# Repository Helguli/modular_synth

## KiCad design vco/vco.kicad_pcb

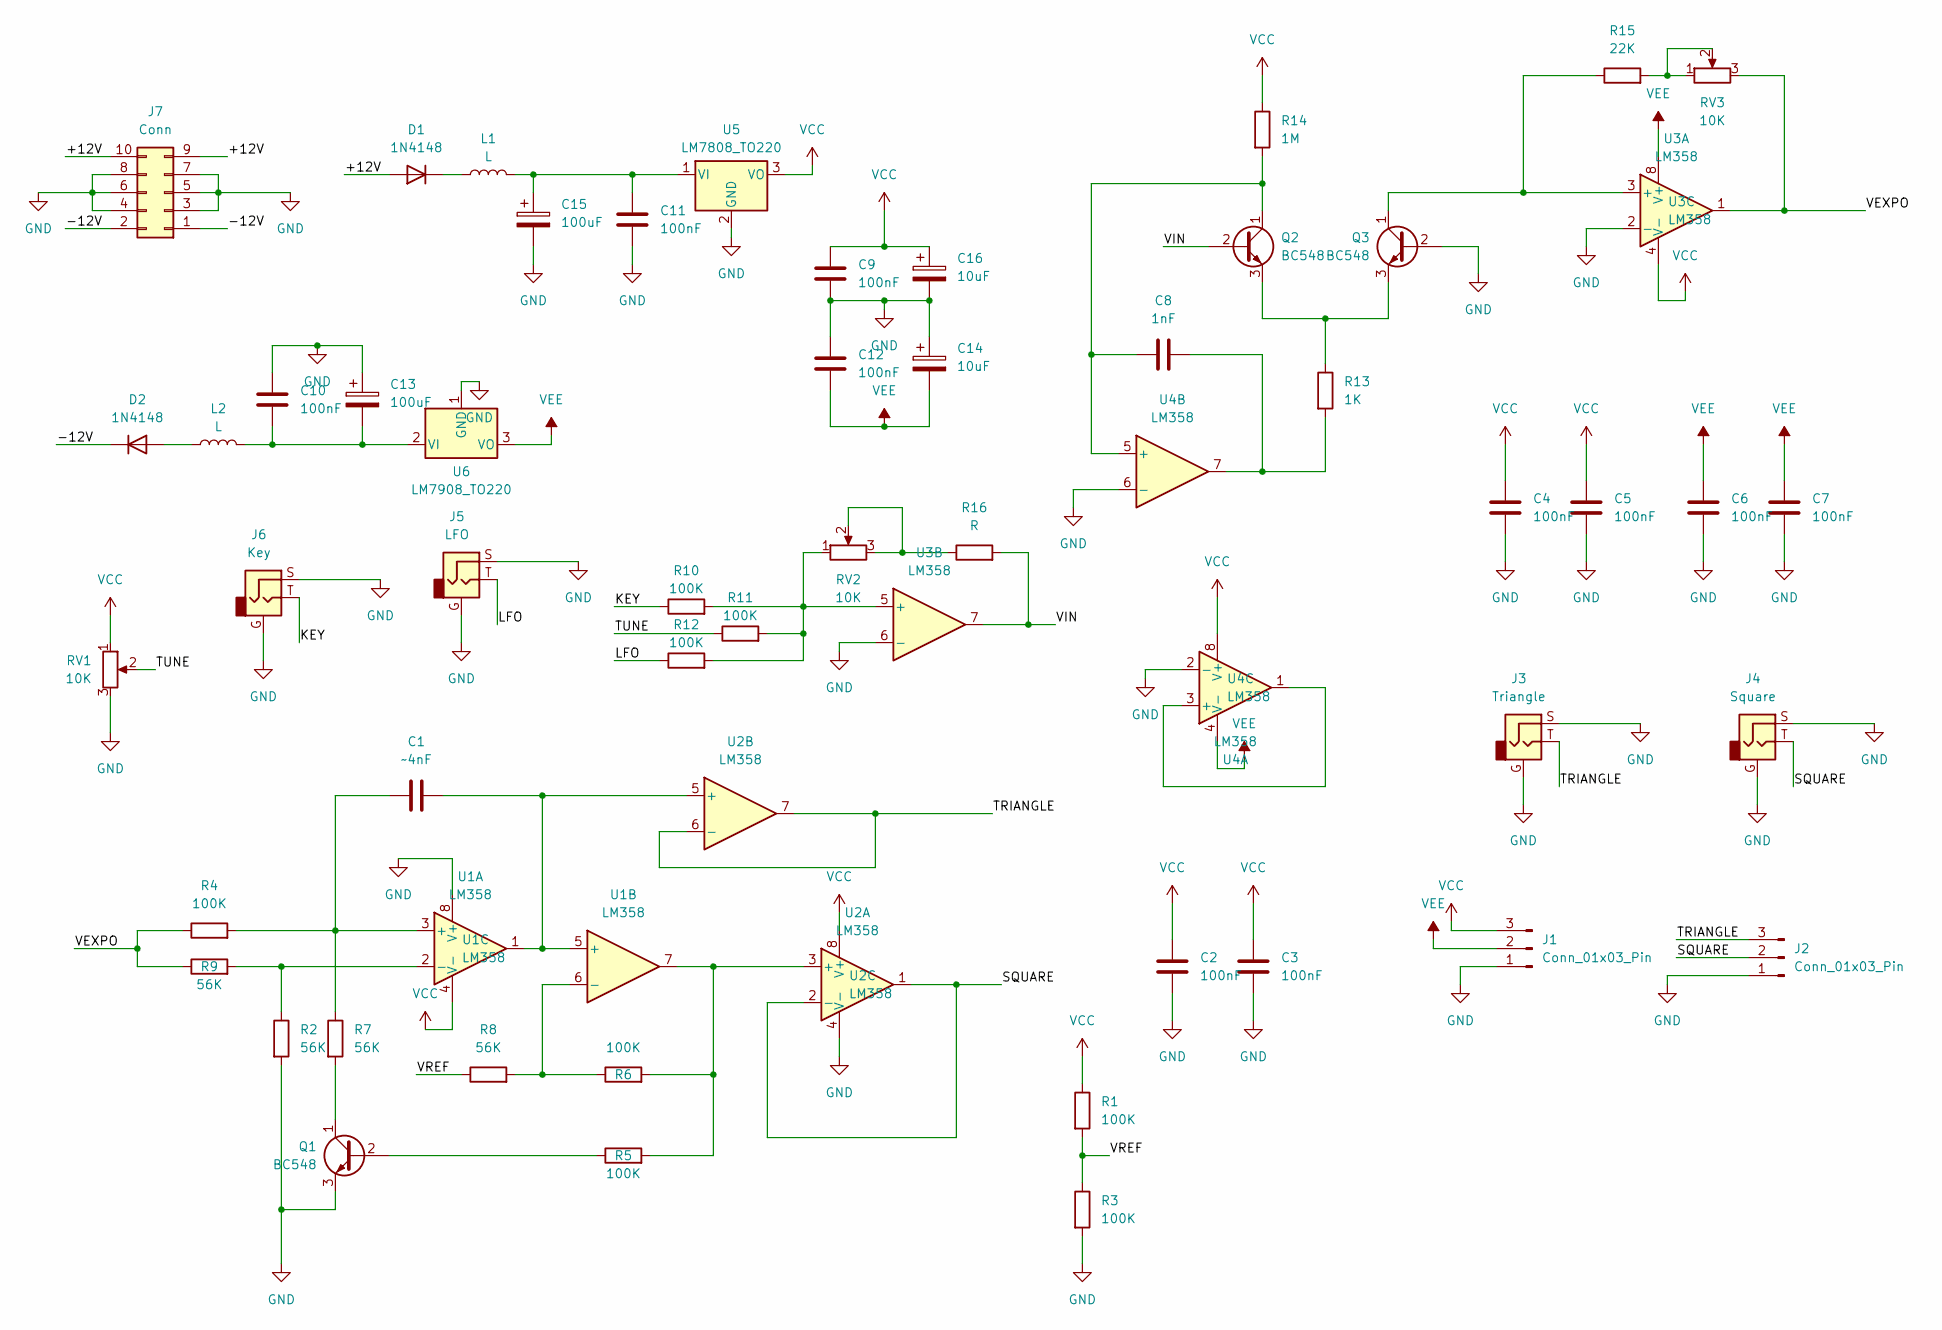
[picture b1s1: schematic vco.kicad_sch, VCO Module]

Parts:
C1: ~4nF; C_1206_3216Metric_Pad1.33x1.80mm_HandSolder
C2, C3, C4, C5, C6, C7, C9, C10, C11, C12: 100nF; C_1206_3216Metric_Pad1.33x1.80mm_HandSolder
C8: 1nF; C_1206_3216Metric_Pad1.33x1.80mm_HandSolder
C13, C15: 100uF; CP_Radial_D8.0mm_P3.80mm
C14, C16: 10uF; CP_Radial_D5.0mm_P2.50mm
D1, D2: 1N4148; D_DO-35_SOD27_P7.62mm_Horizontal
J1, J2: Conn_01x03_Pin; PinHeader_1x03_P2.54mm_Vertical
J3: Triangle; Jack_3.5mm_QingPu_WQP-PJ398SM_Vertical_CircularHoles
J4: Square; Jack_3.5mm_QingPu_WQP-PJ398SM_Vertical_CircularHoles
J5: LFO; Jack_3.5mm_QingPu_WQP-PJ398SM_Vertical_CircularHoles
J6: Key; Jack_3.5mm_QingPu_WQP-PJ398SM_Vertical_CircularHoles
J7: Conn; PinHeader_2x05_P2.54mm_Vertical
L1, L2: L; L_Axial_L6.6mm_D2.7mm_P10.16mm_Horizontal_Vishay_IM-2
Q1, Q2, Q3: BC548; TO-92_Inline_Wide_Big
R1, R3, R4, R5, R6, R10, R11, R12: 100K; R_1206_3216Metric_Pad1.30x1.75mm_HandSolder
R2, R7, R8, R9: 56K; R_1206_3216Metric_Pad1.30x1.75mm_HandSolder
R13: 1K; R_1206_3216Metric_Pad1.30x1.75mm_HandSolder
R14: 1M; R_1206_3216Metric_Pad1.30x1.75mm_HandSolder
R15: 22K; R_1206_3216Metric_Pad1.30x1.75mm_HandSolder
R16: R; R_1206_3216Metric_Pad1.30x1.75mm_HandSolder
RV1: 10K; Potentiometer_Bourns_PTV09A-1_Single_Vertical
RV2, RV3: 10K; Potentiometer_Bourns_3296W_Vertical
U1, U2, U3, U4: LM358; DIP-8_W7.62mm_LongPads
U5: LM7808_TO220; TO-220-3_Vertical
U6: LM7908_TO220; TO-220-3_Vertical

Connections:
/+12V: D1.2 (A), J7.9, J7.10
/-12V: D2.1 (K), J7.1, J7.2
/KEY: J6.T, R10.1
/LFO: J5.T, R12.1
/SQUARE: J2.2, J4.T, U2.1, U2.2 (-)
/TRIANGLE: J2.3, J3.T, U2.6 (-), U2.7
/TUNE: R11.1, RV1.2
/VEXPO: R4.1, R9.1, RV3.3, U3.1
/VIN: Q2.2 (B), R16.2, U3.7
/VREF: R1.2, R3.1, R8.1
GND: C2.2, C3.2, C4.2, C5.2, C6.2, C7.2, C9.2, C10.1, C11.2, C12.1, C13.1, C14.1, C15.2, C16.2, J1.1, J2.1, J3.G, J3.S, J4.G, J4.S, J5.G, J5.S, J6.G, J6.S, J7.3, J7.4, J7.5, J7.6, J7.7, J7.8, Q1.3 (E), Q3.2 (B), R2.2, R3.2, RV1.3, U1.8 (V+), U2.4 (V-), U3.2 (-), U3.6 (-), U4.2 (-), U4.6 (-), U5.2 (GND), U6.1 (GND)
unnamed: C8.2, R13.2, U4.7
unnamed: D1.1 (K), L1.1
unnamed: D2.2 (A), L2.1
unnamed: Q1.2 (B), R5.1
unnamed: Q1.1 (C), R7.2
unnamed: C8.1, Q2.1 (C), R14.2, U4.5 (+)
unnamed: Q2.3 (E), Q3.3 (E), R13.1
unnamed: Q3.1 (C), R15.1, U3.3 (+)
unnamed: R15.2, RV3.1, RV3.2
unnamed: R16.1, RV2.2, RV2.3
unnamed: C1.1, R4.2, R7.1, U1.3 (+)
unnamed: R2.1, R9.2, U1.2 (-)
unnamed: C1.2, U1.1, U1.5 (+), U2.5 (+)
unnamed: R6.1, R8.2, U1.6 (-)
unnamed: R5.2, R6.2, U1.7, U2.3 (+)
unnamed: R10.2, R11.2, R12.2, RV2.1, U3.5 (+)
unnamed: U4.1, U4.3 (+)
unnamed: C11.1, C15.1, L1.2, U5.1 (VI)
unnamed: C10.2, C13.2, L2.2, U6.2 (VI)
VCC: C2.1, C3.1, C4.1, C5.1, C9.1, C16.1, J1.3, R1.1, R14.1, RV1.1, U1.4 (V-), U2.8 (V+), U3.4 (V-), U4.8 (V+), U5.3 (VO)
VEE: C6.1, C7.1, C12.2, C14.2, J1.2, U3.8 (V+), U4.4 (V-), U6.3 (VO)

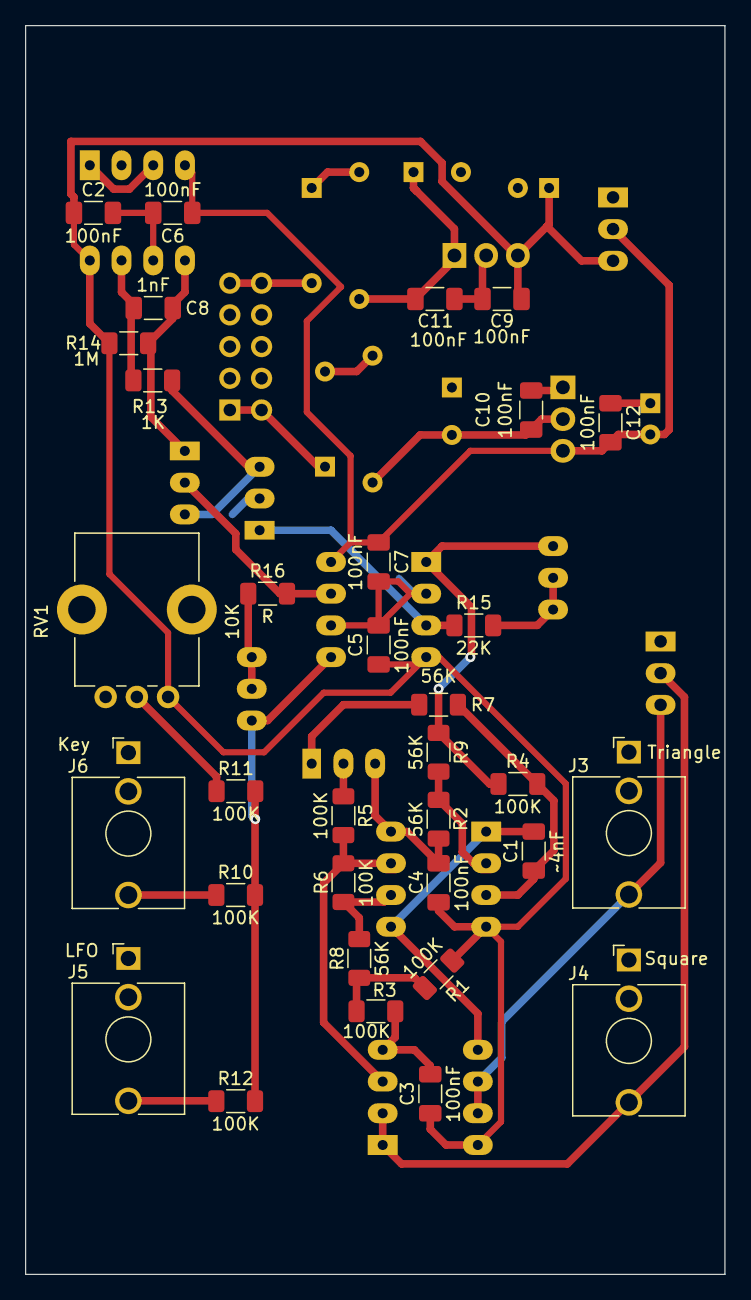
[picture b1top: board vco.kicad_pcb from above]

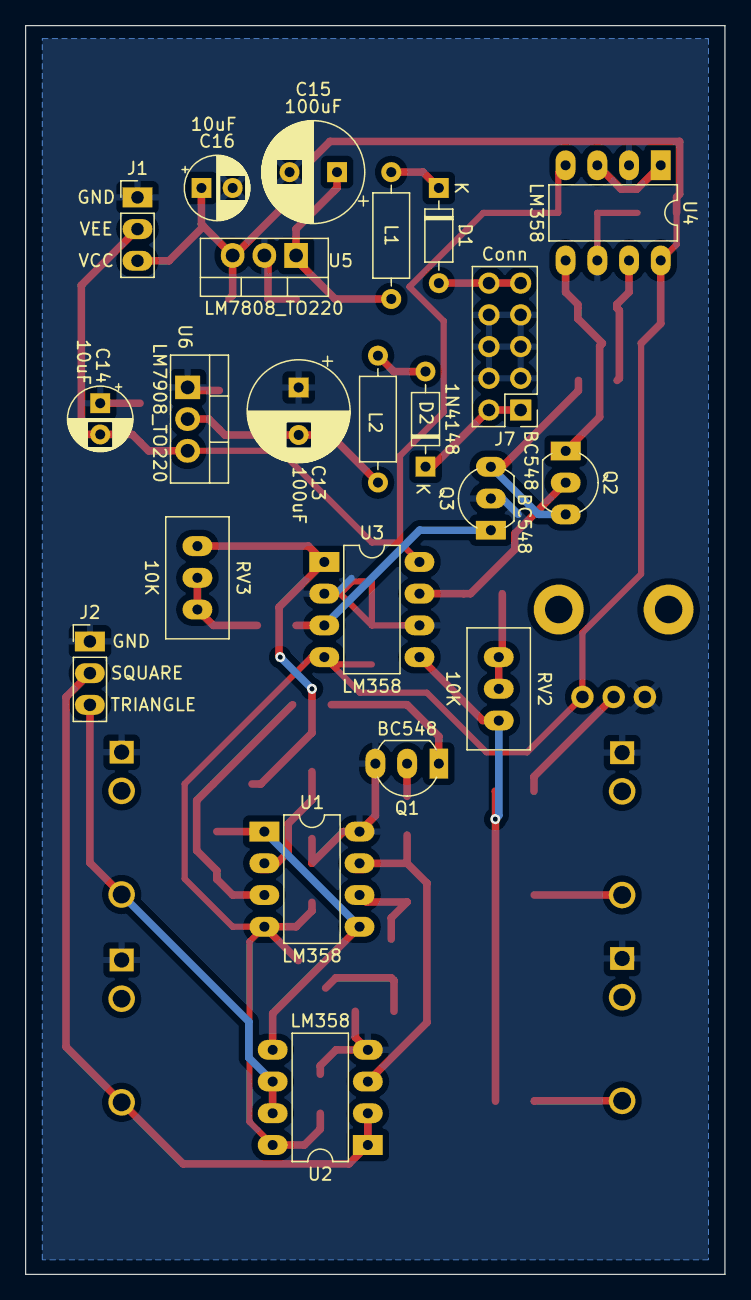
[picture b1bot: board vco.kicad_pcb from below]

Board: 2 copper layers, 56.0 x 100.0 mm, 55 parts (22 on the bottom side), 32 nets.
